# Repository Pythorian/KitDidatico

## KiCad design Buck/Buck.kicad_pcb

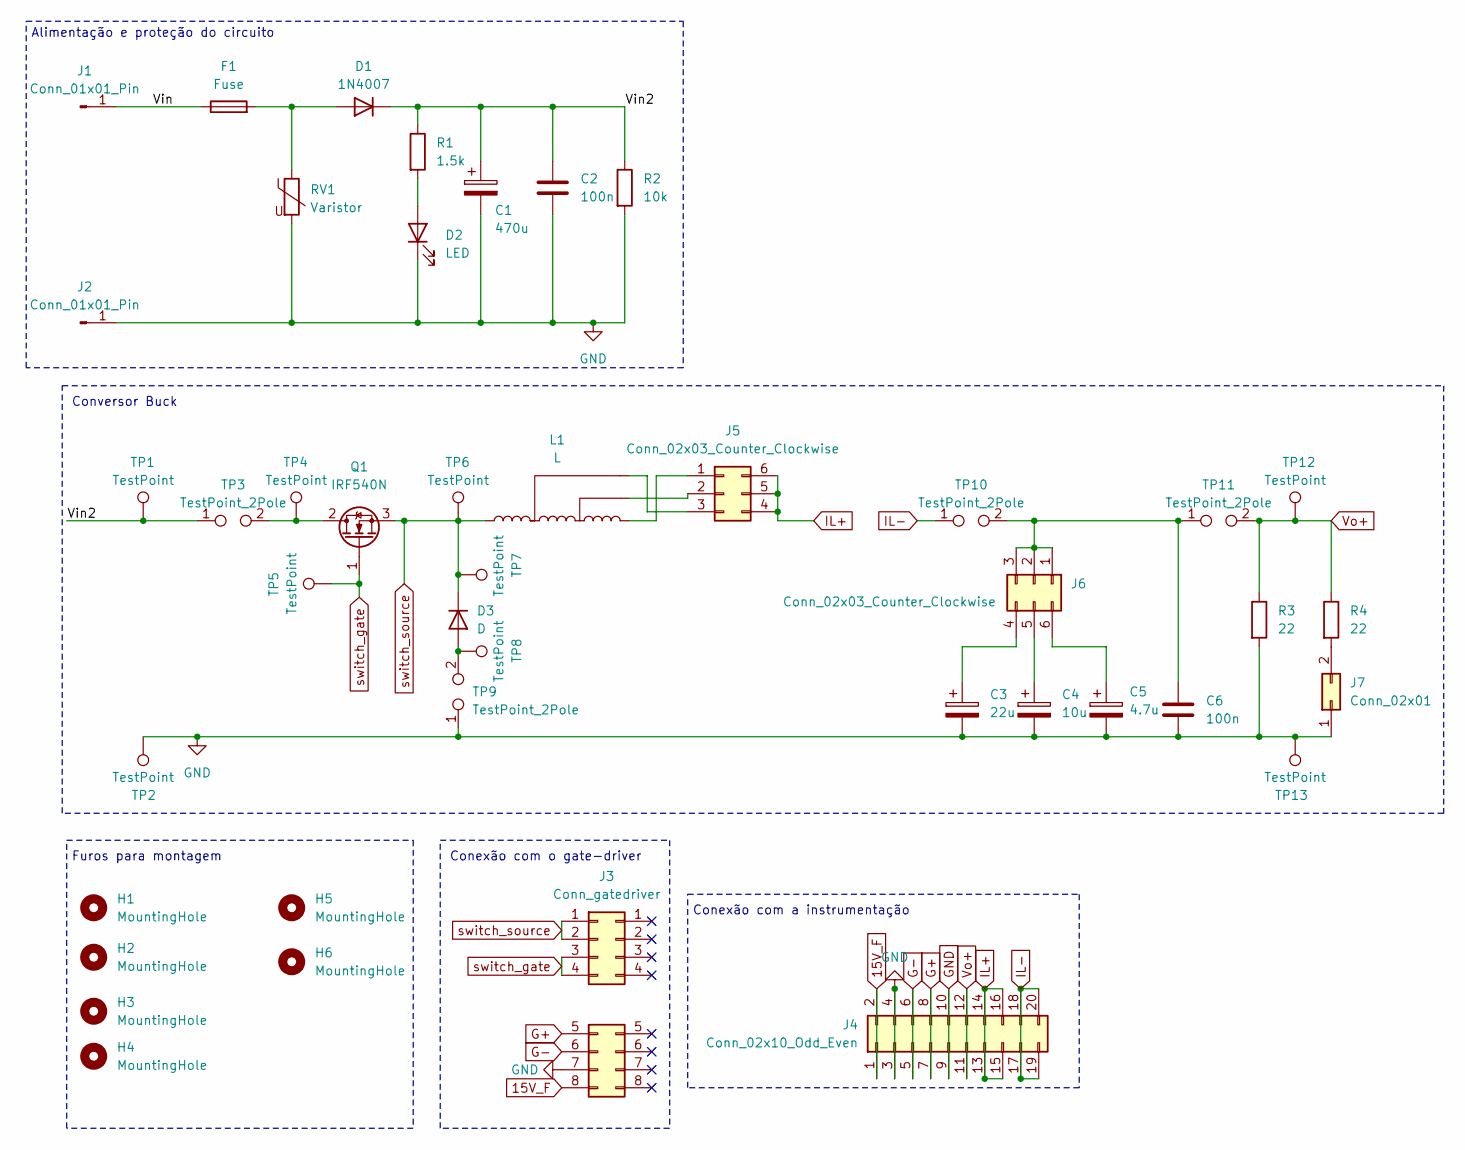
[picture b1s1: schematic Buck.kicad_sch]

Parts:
C1: 470u; CP_Radial_D16.0mm_P7.50mm
C2, C6: 100n; C_Disc_D5.0mm_W2.5mm_P5.00mm
C3: 22u; CP_Radial_D6.3mm_P2.50mm
C4: 10u; CP_Radial_D5.0mm_P2.00mm
C5: 4.7u; CP_Radial_D5.0mm_P2.00mm
D1: 1N4007; D_DO-41_SOD81_P10.16mm_Horizontal
D2: LED; LED_D3.0mm
D3: D; TO-220-2_Horizontal_TabDown
F1: Fuse
H1, H2, H3, H4, H5, H6: MountingHole; Furo
J1, J2: Conn_01x01_Pin; Banana_Jack_1Pin
J3: Conn_gatedriver; GateDriver
J4: Conn_02x10_Odd_Even; PinSocket_2x10_P2.54mm_Horizontal
J5, J6: Conn_02x03_Counter_Clockwise; PinHeader_2x03_P2.54mm_Vertical
J7: Conn_02x01; PinHeader_2x02_P2.54mm_Vertical
L1: L; Inductor_buck
Q1: IRF540N; TO-220-3_Horizontal_TabDown
R1: 1.5k; R_Axial_DIN0204_L3.6mm_D1.6mm_P7.62mm_Horizontal
R2: 10k; R_Axial_DIN0204_L3.6mm_D1.6mm_P7.62mm_Horizontal
R3, R4: 22; R_Axial_Power_L50.0mm_W9.0mm_P55.88mm
RV1: Varistor; RV_Disc_D7mm_W3.4mm_P5mm
TP1, TP2, TP4, TP5, TP6, TP7, TP8, TP12, TP13: TestPoint; TestPoint_Loop_D2.60mm_Drill1.6mm_Beaded
TP3, TP9, TP10, TP11: TestPoint_2Pole; Testpoint_current

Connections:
15V_F: J3.8 (Pin_15), J4.1, J4.2
/Vin: F1.1, J1.1
/Vin2: C1.1, C2.1, D1.1 (K), R1.1, R2.1, TP1.1, TP3.1
G+: J3.5 (Pin_9), J4.7, J4.8
G-: J3.6 (Pin_11), J4.5, J4.6
GND: C1.2, C2.2, C3.2, C4.2, C5.2, C6.2, D2.1 (K), J2.1, J3.7 (Pin_13), J4.3, J4.4, J4.9, J4.10, J7.1, R2.2, R3.2, RV1.2, TP2.1, TP9.1, TP13.1; also elsewhere on the board
IL+: J4.13, J4.14, J4.15, J4.16, J5.4, J5.5, J5.6
IL-: J4.17, J4.18, J4.19, J4.20, TP10.1
unnamed: D1.2 (A), F1.2, RV1.1
unnamed: D2.2 (A), R1.2
unnamed: D3.2 (A), TP8.1, TP9.2
unnamed: J5.1, L1.4
unnamed: J5.2, L1.3
unnamed: J5.3, L1.2
unnamed: C6.1, J6.1, J6.2, J6.3, TP10.2, TP11.1
unnamed: C3.1, J6.4
unnamed: C4.1, J6.5
unnamed: C5.1, J6.6
unnamed 18: J7.2, R4.2; also elsewhere on the board
unnamed: Q1.2 (D), TP3.2, TP4.1
Vo+: J4.11, J4.12, R3.1, R4.1, TP11.2, TP12.1; also elsewhere on the board
switch_gate: J3.3 (Pin_5), J3.4 (Pin_7), Q1.1 (G), TP5.1
switch_source: D3.1 (K), J3.1, J3.2 (Pin_3), L1.1, Q1.3 (S), TP6.1, TP7.1

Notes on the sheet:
Conversor Buck
Conexão com o gate-driver
Alimentação e proteção do circuito
Furos para montagem
Conexão com a instrumentação

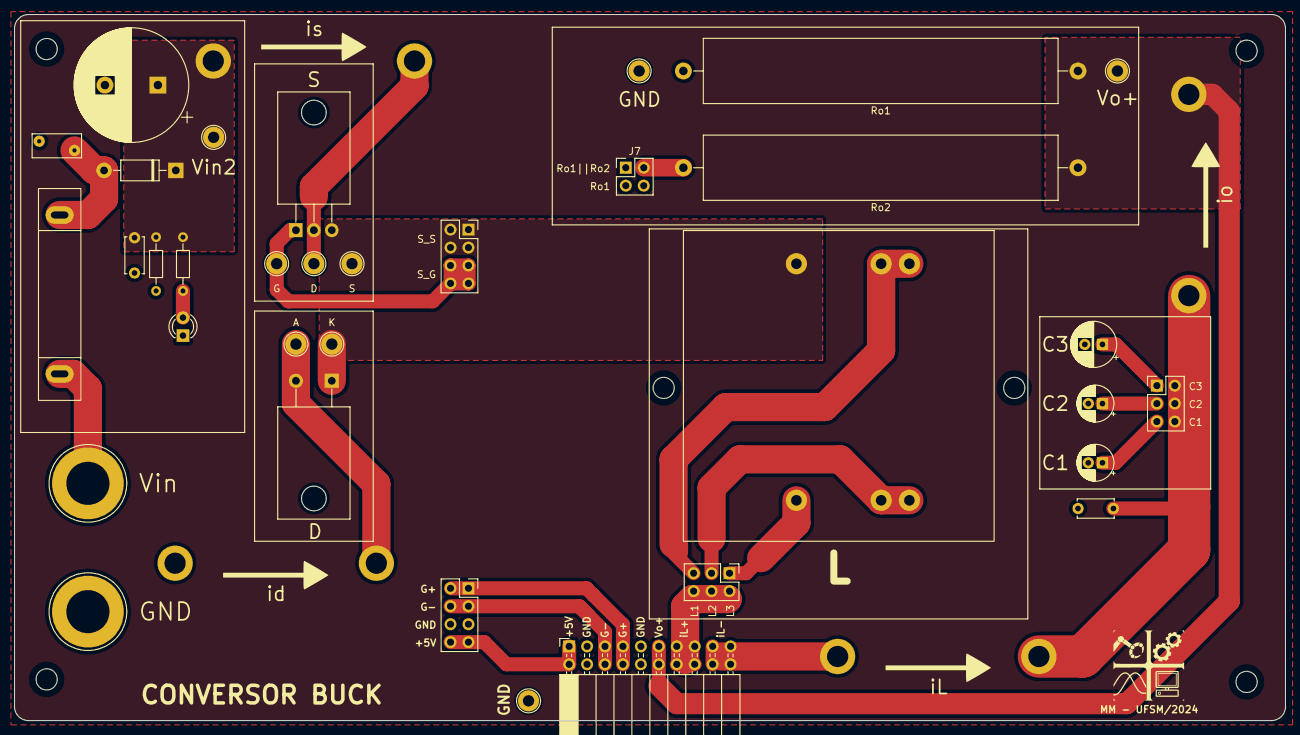
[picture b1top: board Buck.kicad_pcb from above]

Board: 2 copper layers, 180.0 x 100.0 mm, 43 parts (0 on the bottom side), 23 nets.

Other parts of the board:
Ro1, Ro2: 22; R_Axial_Power_L50.0mm_W9.0mm_P55.88mm

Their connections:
GND: Ro1.2; also elsewhere on the board
unnamed 18: Ro2.2; also elsewhere on the board
Vo+: Ro1.1, Ro2.1; also elsewhere on the board

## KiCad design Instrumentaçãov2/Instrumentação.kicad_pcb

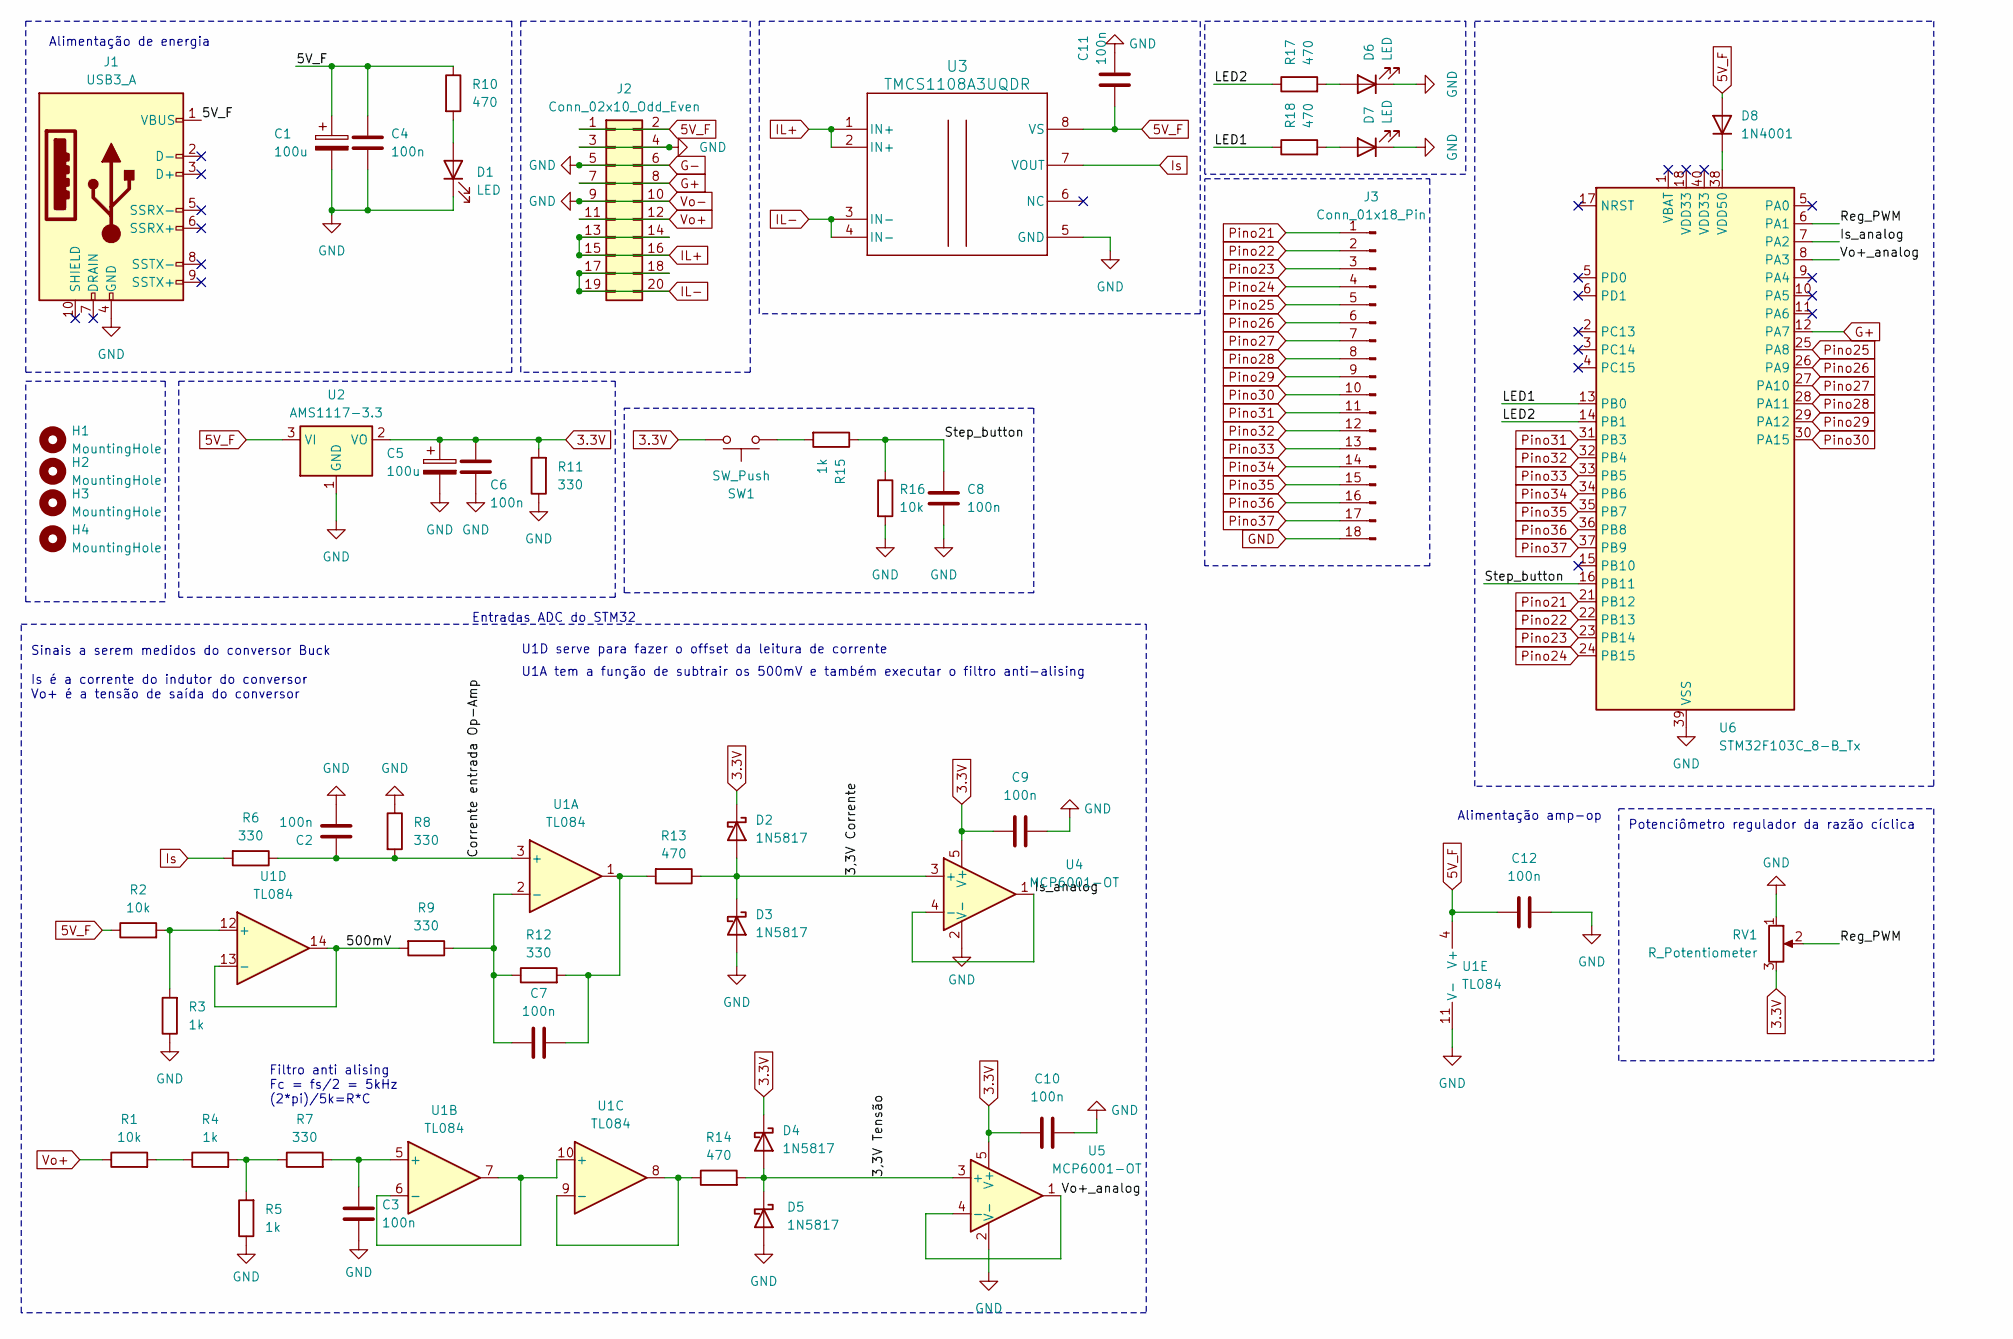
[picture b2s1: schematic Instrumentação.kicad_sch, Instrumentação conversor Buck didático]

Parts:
C1, C5: 100u; CP_Radial_D6.3mm_P2.50mm
C2, C3, C4, C6, C7, C8, C9, C10, C11, C12: 100n; C_Disc_D5.0mm_W2.5mm_P5.00mm
D1, D6, D7: LED; LED_D3.0mm
D2, D3, D4, D5: 1N5817; D_DO-41_SOD81_P10.16mm_Horizontal
D8: 1N4001; D_DO-41_SOD81_P10.16mm_Horizontal
H1, H2, H3, H4: MountingHole; Furo
J1: USB3_A; USB_A_Molex_67643_Horizontal
J2: Conn_02x10_Odd_Even; PinHeader_2x10_P2.54mm_Horizontal
J3: Conn_01x18_Pin; PinHeader_1x18_P2.54mm_Vertical
R1, R2, R16: 10k; R_Axial_DIN0204_L3.6mm_D1.6mm_P7.62mm_Horizontal
R3, R4, R5, R15: 1k; R_Axial_DIN0204_L3.6mm_D1.6mm_P7.62mm_Horizontal
R6, R7, R8, R9, R11, R12: 330; R_Axial_DIN0204_L3.6mm_D1.6mm_P7.62mm_Horizontal
R10, R13, R14, R17, R18: 470; R_Axial_DIN0204_L3.6mm_D1.6mm_P7.62mm_Horizontal
RV1: R_Potentiometer; Potentiometer_Alps_RK163_Single_Horizontal
SW1: SW_Push; SW_PUSH_6mm
U1: TL084; DIP-14_W7.62mm_Socket
U2: AMS1117-3.3; SOT-223-3_TabPin2
U3: TMCS1108A3UQDR; D0008A-IPC_A
U4, U5: MCP6001-OT; SOT-23-5
U6: STM32F103C_8-B_Tx; DIP-40_W15.24mm_Socket_LongPads

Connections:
3.3V: C5.1, C6.2, C9.1, C10.1, D2.1 (K), D4.1 (K), R11.2, RV1.3, SW1.2, U2.2 (VO), U4.5 (V+), U5.5 (V+)
5V_F: C1.1, C4.2, C11.2, C12.2, D8.2 (A), J1.1 (VBUS), J2.1, J2.2, R2.1, R10.1, U1.4 (V+), U2.3 (VI), U3.8 (VS)
/3,3V Corrente: D2.2 (A), D3.1 (K), R13.1, U4.3 (+)
/3,3V Tensão: D4.2 (A), D5.1 (K), R14.2, U5.3 (+)
/500mV: R9.2, U1.13 (-), U1.14
/Corrente entrada Op-Amp: C2.2, R6.1, R8.2, U1.3 (+)
/Is_analog: U4.1, U4.4 (-), U6.7 (PA2)
/LED1: R18.1, U6.13 (PB0)
/LED2: R17.1, U6.14 (PB1)
/Reg_PWM: RV1.2, U6.6 (PA1)
/Step_button: C8.2, R15.1, R16.1, U6.16 (PB11)
/Vo+_analog: U5.1, U5.4 (-), U6.8 (PA3)
G+: J2.7, J2.8, U6.12 (PA7)
G-: C1.2, C2.1, C3.1, C4.1, C5.2, C6.1, C8.1, C9.2, C10.2, C11.1, C12.1, D1.1 (K), D3.2 (A), D5.2 (A), D6.1 (K), D7.1 (K), J1.4 (GND), J2.3, J2.4, J2.5, J2.6, J2.9, J2.10, J3.18, R3.1, R5.1, R8.1, R11.1, R16.2, RV1.1, U1.11 (V-), U2.1 (GND), U3.5 (GND), U4.2 (V-), U5.2 (V-), U6.19 (VSS), U6.20 (VSS), U6.39 (VSS)
IL+: J2.13, J2.14, J2.15, J2.16, U3.1 (IN+), U3.2 (IN+)
IL-: J2.17, J2.18, J2.19, J2.20, U3.3 (IN-), U3.4 (IN-)
Is: R6.2, U3.7 (VOUT)
unnamed: C7.2, R12.2, R13.2, U1.1
unnamed: D1.2 (A), R10.2
unnamed: D6.2 (A), R17.2
unnamed: D7.2 (A), R18.2
unnamed: D8.1 (K), U6.38 (VDD50)
unnamed: R1.2, R4.1
unnamed: R4.2, R5.2, R7.1
unnamed: R15.2, SW1.1
unnamed: C7.1, R9.1, R12.1, U1.2 (-)
unnamed: C3.2, R7.2, U1.5 (+)
unnamed: U1.6 (-), U1.7, U1.10 (+)
unnamed: R14.1, U1.8, U1.9 (-)
unnamed: R2.2, R3.2, U1.12 (+)
Pino21: J3.1, U6.21 (PB12)
Pino22: J3.2, U6.22 (PB13)
Pino23: J3.3, U6.23 (PB14)
Pino24: J3.4, U6.24 (PB15)
Pino25: J3.5, U6.25 (PA8)
Pino26: J3.6, U6.26 (PA9)
Pino27: J3.7, U6.27 (PA10)
Pino28: J3.8, U6.28 (PA11)
Pino29: J3.9, U6.29 (PA12)
Pino30: J3.10, U6.30 (PA15)
Pino31: J3.11, U6.31 (PB3)
Pino32: J3.12, U6.32 (PB4)
Pino33: J3.13, U6.33 (PB5)
Pino34: J3.14, U6.34 (PB6)
Pino35: J3.15, U6.35 (PB7)
Pino36: J3.16, U6.36 (PB8)
Pino37: J3.17, U6.37 (PB9)
Vo+: J2.11, J2.12, R1.1

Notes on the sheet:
U1D serve para fazer o offset da leitura de corrente
Alimentação de energia
Potenciômetro regulador da razão cíclica
Sinais a serem medidos do conversor Buck Is é a corrente do indutor do conversor Vo+ é a tensão de saída do conversor
Entradas ADC do STM32
Alimentação amp-op
Filtro anti alising Fc = fs/2 = 5kHz (2*pi)/5k=R*C
U1A tem a função de subtrair os 500mV e também executar o filtro anti-alising

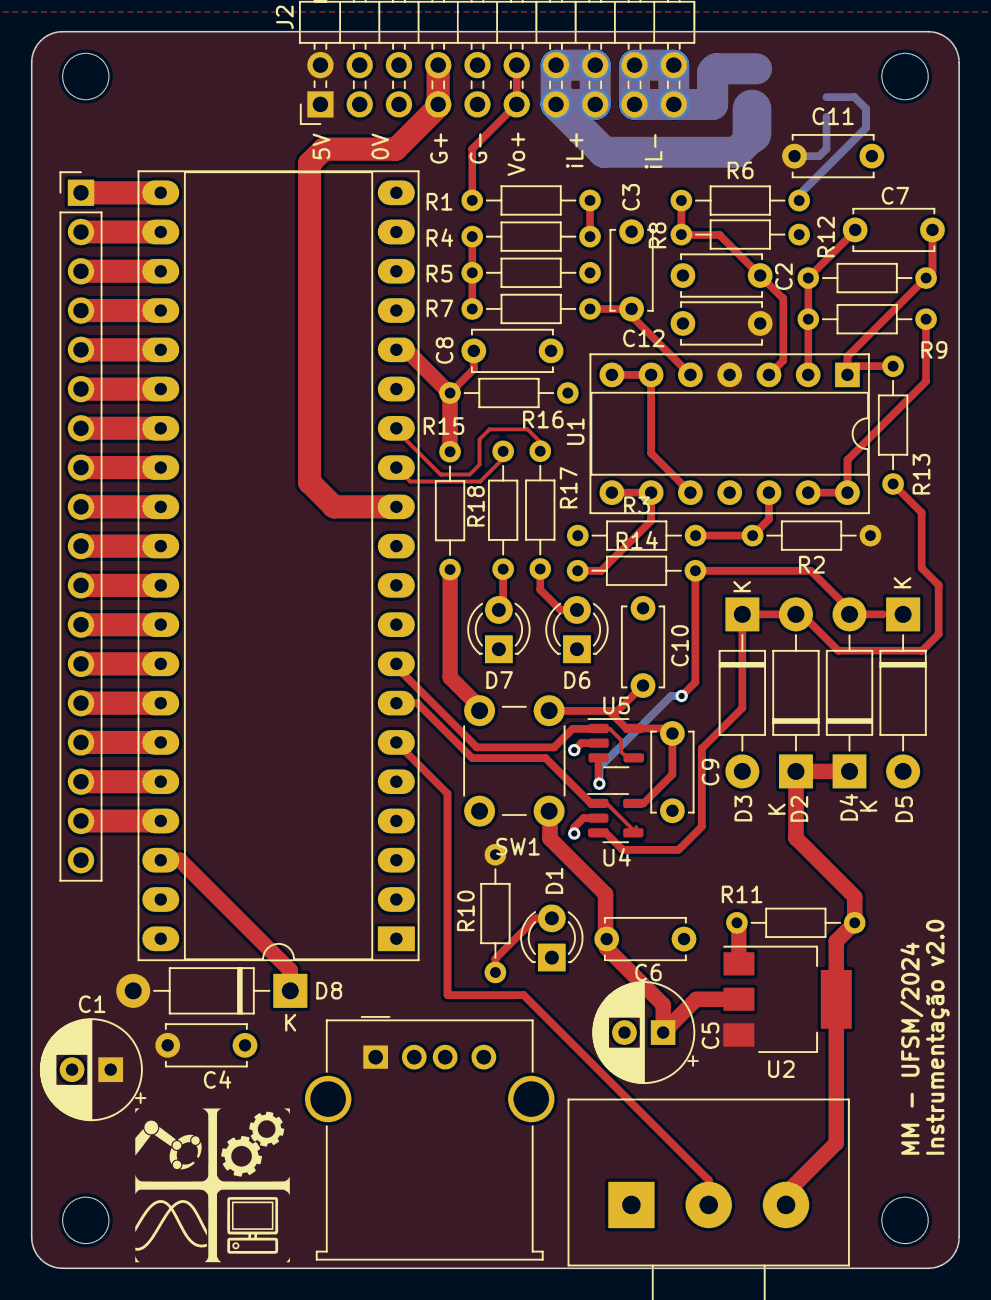
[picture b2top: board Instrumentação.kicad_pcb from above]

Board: 2 copper layers, 60.0 x 80.0 mm, 53 parts (1 on the bottom side), 48 nets.

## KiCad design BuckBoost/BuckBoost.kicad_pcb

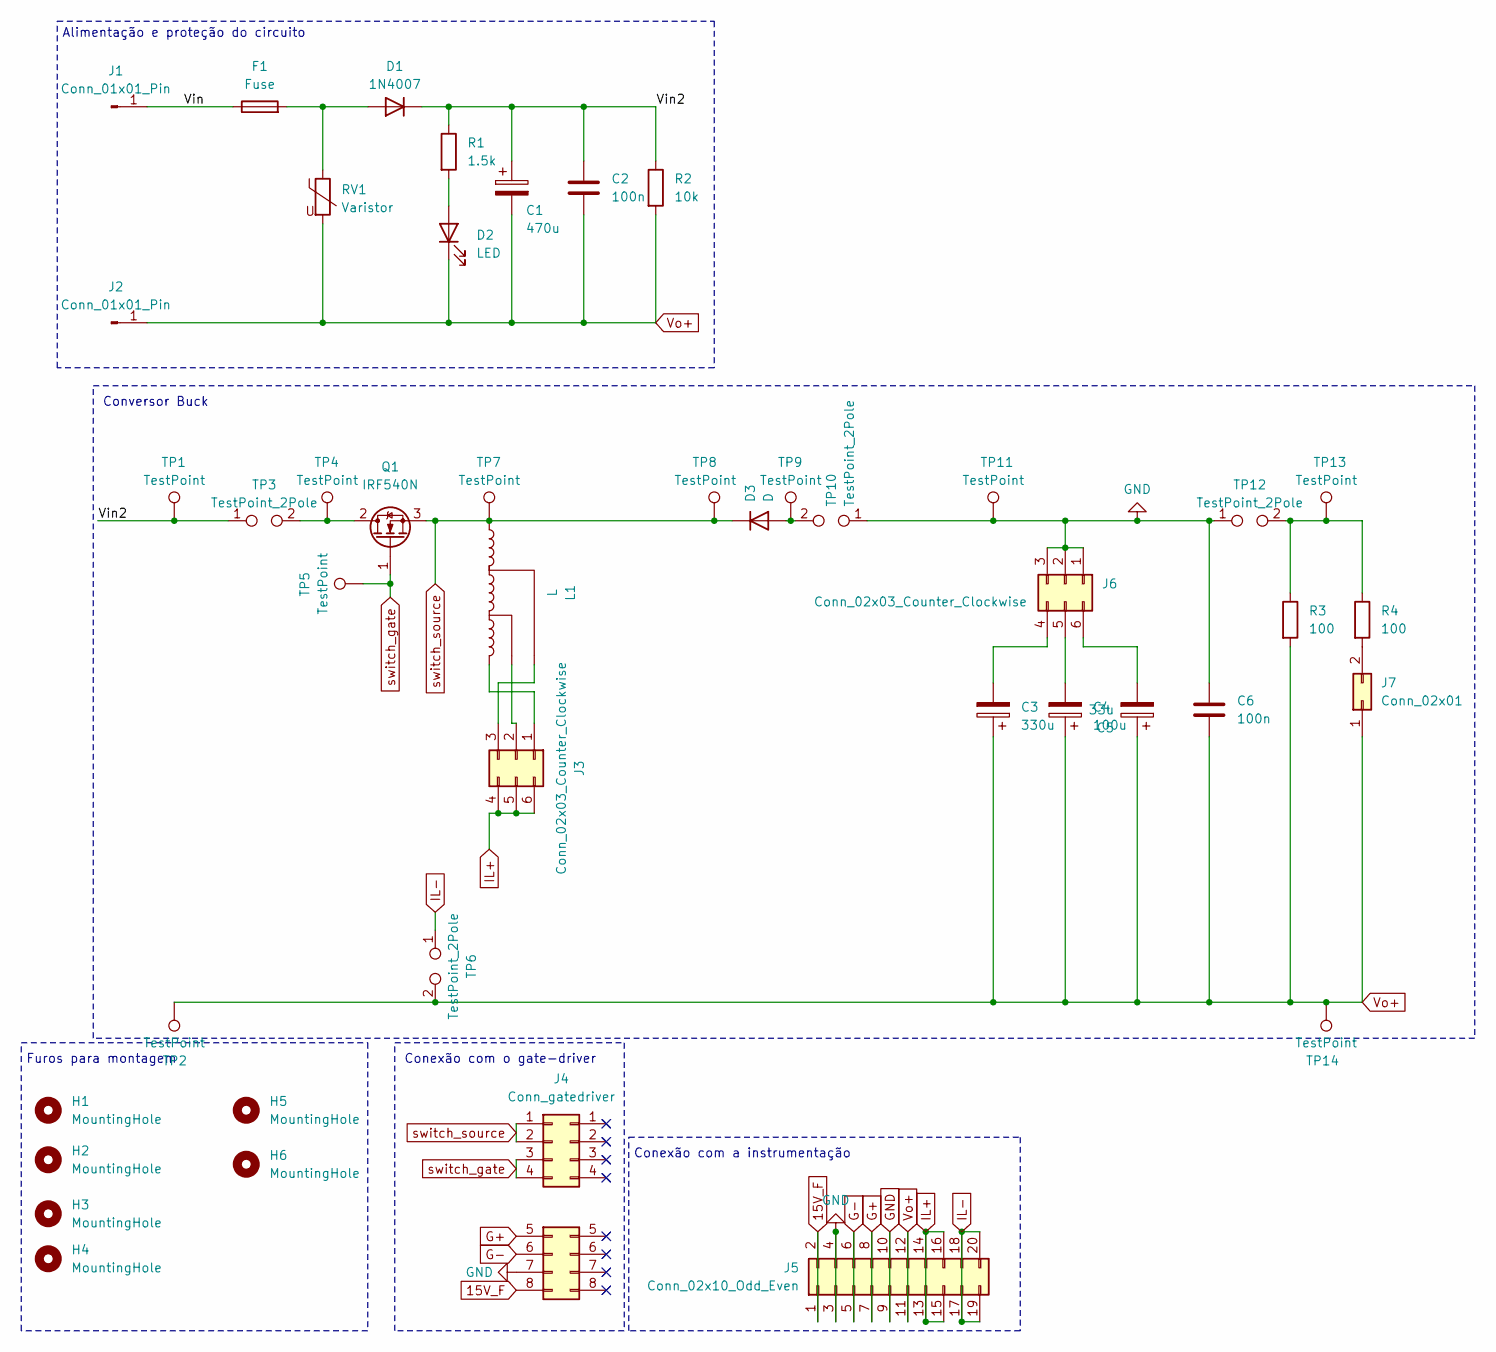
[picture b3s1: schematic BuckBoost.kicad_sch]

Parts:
C1: 470u; CP_Radial_D16.0mm_P7.50mm
C2, C6: 100n; C_Disc_D5.0mm_W2.5mm_P5.00mm
C3: 330u; CP_Radial_D10.0mm_P5.00mm
C4: 100u; CP_Radial_D10.0mm_P5.00mm
C5: 33u; CP_Radial_D6.3mm_P2.50mm
D1: 1N4007; D_DO-41_SOD81_P10.16mm_Horizontal
D2: LED; LED_D3.0mm
D3: D; TO-220-2_Horizontal_TabDown
F1: Fuse
H1, H2, H3, H4, H5, H6: MountingHole; Furo
J1, J2: Conn_01x01_Pin; Banana_Jack_1Pin
J3, J6: Conn_02x03_Counter_Clockwise; PinHeader_2x03_P2.54mm_Vertical
J4: Conn_gatedriver; GateDriver
J5: Conn_02x10_Odd_Even; PinSocket_2x10_P2.54mm_Horizontal
J7: Conn_02x01; PinHeader_2x02_P2.54mm_Vertical
L1: L; Inductor_buckboost
Q1: IRF540N; TO-220-3_Horizontal_TabDown
R1: 1.5k; R_Axial_DIN0204_L3.6mm_D1.6mm_P7.62mm_Horizontal
R2: 10k; R_Axial_DIN0204_L3.6mm_D1.6mm_P7.62mm_Horizontal
R3, R4: 100; R_Axial_Power_L50.0mm_W9.0mm_P55.88mm
RV1: Varistor; RV_Disc_D7mm_W3.4mm_P5mm
TP1, TP2, TP4, TP5, TP7, TP8, TP9, TP11, TP13, TP14: TestPoint; TestPoint_Loop_D2.60mm_Drill1.6mm_Beaded
TP3, TP6, TP10, TP12: TestPoint_2Pole; Testpoint_current

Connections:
15V_F: J4.8 (Pin_15), J5.1, J5.2
/Vin: F1.1, J1.1
/Vin2: C1.1, C2.1, D1.1 (K), R1.1, R2.1, TP1.1, TP3.1; also elsewhere on the board
G+: J4.5 (Pin_9), J5.7, J5.8
G-: J4.6 (Pin_11), J5.5, J5.6
GND: C6.1, J4.7 (Pin_13), J5.3, J5.4, J5.9, J5.10, J6.1, J6.2, J6.3, TP10.1, TP11.1, TP12.1
IL+: J3.4, J3.5, J3.6, J5.13, J5.14, J5.15, J5.16
IL-: J5.17, J5.18, J5.19, J5.20, TP6.1
unnamed: D1.2 (A), F1.2, RV1.1
unnamed: D2.2 (A), R1.2
unnamed: D3.2 (A), TP9.1, TP10.2
unnamed 11: J3.1, L1.4; also elsewhere on the board
unnamed 12: J3.2, L1.3; also elsewhere on the board
unnamed 13: J3.3, L1.2; also elsewhere on the board
unnamed: C3.2, J6.4
unnamed: C4.2, J6.5
unnamed: C5.2, J6.6
unnamed 17: J7.2, R4.2; also elsewhere on the board
unnamed: Q1.2 (D), TP3.2, TP4.1
unnamed 19: R3.1, R4.1, TP12.2, TP13.1; also elsewhere on the board
Vo+: C1.2, C2.2, C3.1, C4.1, C5.1, C6.2, D2.1 (K), J2.1, J5.11, J5.12, J7.1, R2.2, R3.2, RV1.2, TP2.1, TP6.2, TP14.1; also elsewhere on the board
switch_gate: J4.3 (Pin_5), J4.4 (Pin_7), Q1.1 (G), TP5.1
switch_source: D3.1 (K), J4.1, J4.2 (Pin_3), L1.1, Q1.3 (S), TP7.1, TP8.1; also elsewhere on the board

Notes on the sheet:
Conversor Buck
Conexão com o gate-driver
Alimentação e proteção do circuito
Furos para montagem
Conexão com a instrumentação

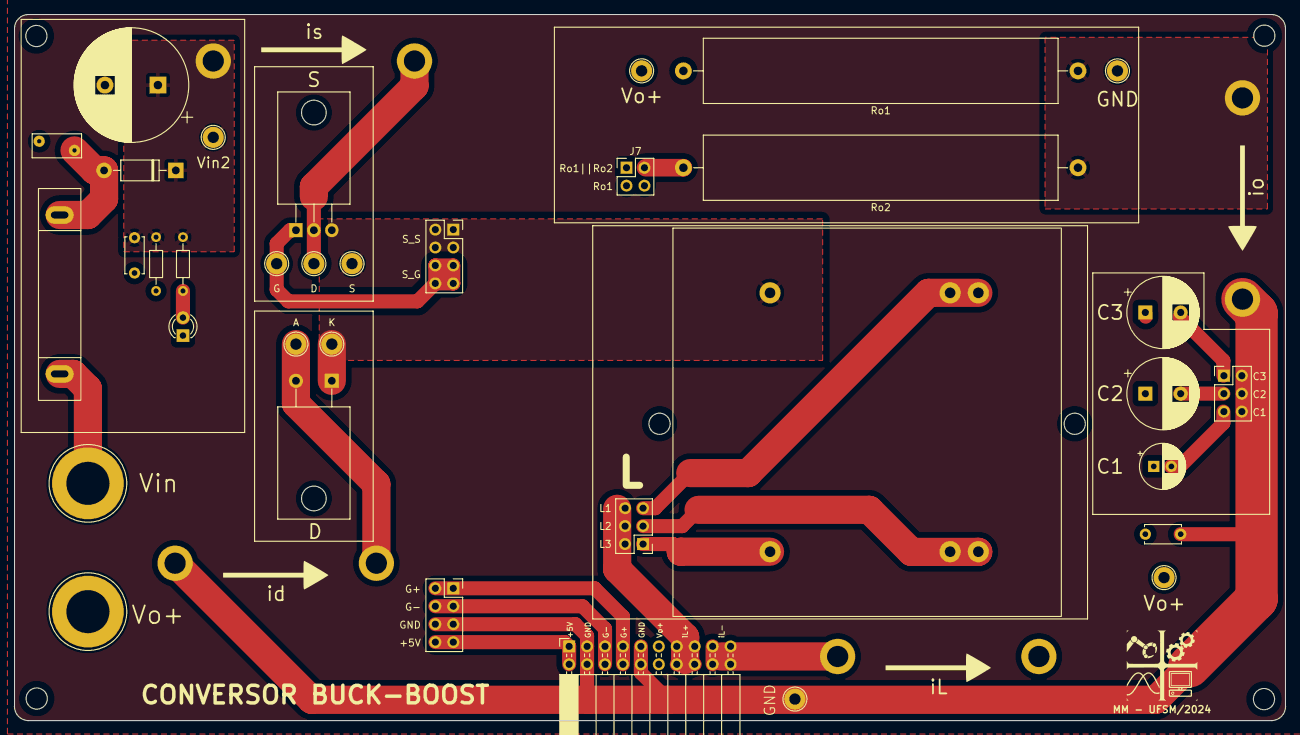
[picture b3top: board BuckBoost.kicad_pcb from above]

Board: 2 copper layers, 180.0 x 100.0 mm, 44 parts (0 on the bottom side), 23 nets.

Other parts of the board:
L: L; Inductor_buckboost
Ro1, Ro2: 100; R_Axial_Power_L50.0mm_W9.0mm_P55.88mm
Vin2: TestPoint; TestPoint_Loop_D2.60mm_Drill1.6mm_Beaded

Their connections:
/Vin2: Vin2.1; also elsewhere on the board
unnamed 11: L.4; also elsewhere on the board
unnamed 12: L.3; also elsewhere on the board
unnamed 13: L.2; also elsewhere on the board
unnamed 17: Ro2.2; also elsewhere on the board
unnamed 19: Ro1.1, Ro2.1; also elsewhere on the board
Vo+: Ro1.2; also elsewhere on the board
switch_source: L.1; also elsewhere on the board

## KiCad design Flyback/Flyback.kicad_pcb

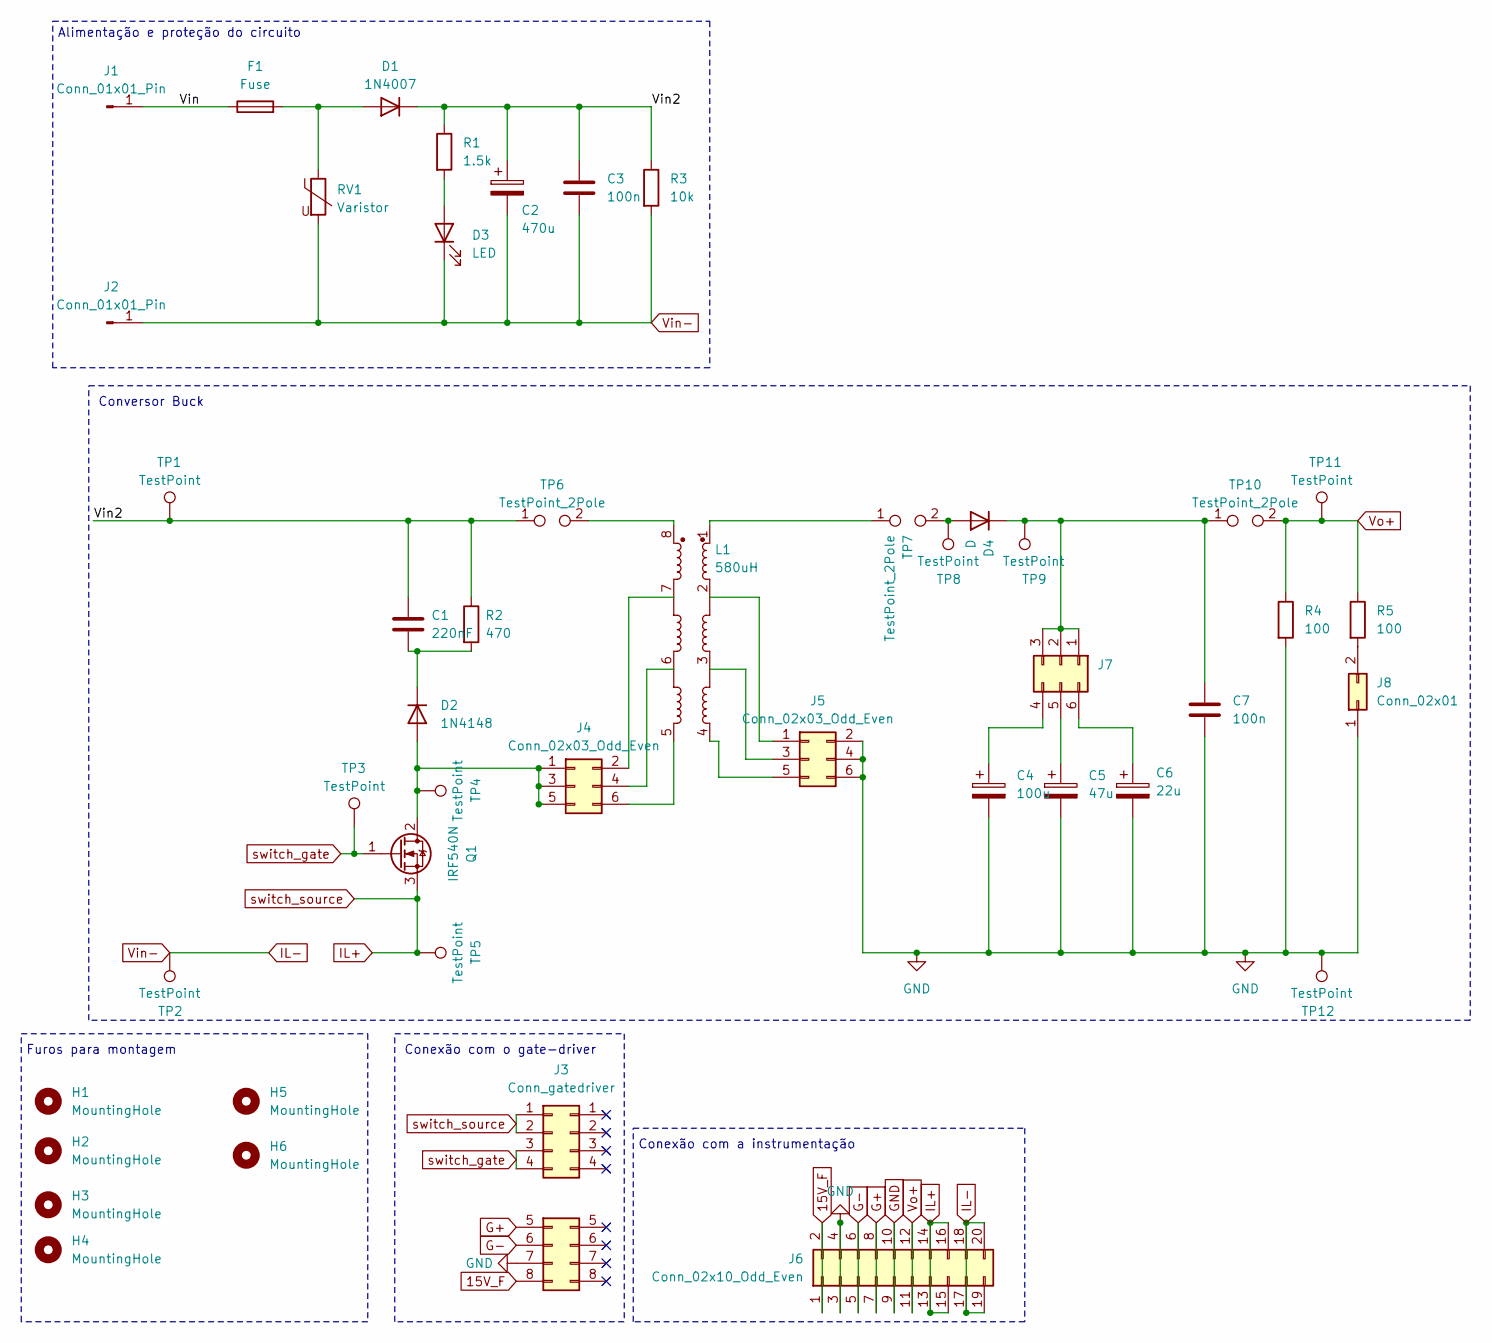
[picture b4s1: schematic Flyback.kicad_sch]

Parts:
C1: 220nF; C_Disc_D5.0mm_W2.5mm_P5.00mm
C2: 470u; CP_Radial_D16.0mm_P7.50mm
C3, C7: 100n; C_Disc_D5.0mm_W2.5mm_P5.00mm
C4: 100u; CP_Radial_D10.0mm_P5.00mm
C5: 47u; CP_Radial_D6.3mm_P2.50mm
C6: 22u; CP_Radial_D6.3mm_P2.50mm
D1: 1N4007; D_DO-41_SOD81_P10.16mm_Horizontal
D2: 1N4148; D_DO-35_SOD27_P7.62mm_Horizontal
D3: LED; LED_D3.0mm
D4: D; TO-220-2_Horizontal_TabDown
F1: Fuse
H1, H2, H3, H4, H5, H6: MountingHole; Furo
J1, J2: Conn_01x01_Pin; Banana_Jack_1Pin
J3: Conn_gatedriver; GateDriver
J4, J5: Conn_02x03_Odd_Even; PinHeader_2x03_P2.54mm_Vertical
J6: Conn_02x10_Odd_Even; PinSocket_2x10_P2.54mm_Horizontal
J7: Conn_02x03_Counter_Clockwise; PinHeader_2x03_P2.54mm_Vertical
J8: Conn_02x01; PinHeader_2x02_P2.54mm_Vertical
L1: 580uH; Transformer_Flyback
Q1: IRF540N; TO-220-3_Horizontal_TabDown
R1: 1.5k; R_Axial_DIN0204_L3.6mm_D1.6mm_P7.62mm_Horizontal
R2: 470; R_Axial_Power_L20.0mm_W6.4mm_P25.40mm
R3: 10k; R_Axial_DIN0204_L3.6mm_D1.6mm_P7.62mm_Horizontal
R4, R5: 100; R_Axial_Power_L50.0mm_W9.0mm_P55.88mm
RV1: Varistor; RV_Disc_D7mm_W3.4mm_P5mm
TP1, TP2, TP3, TP4, TP5, TP8, TP9, TP11, TP12: TestPoint; TestPoint_Loop_D2.60mm_Drill1.6mm_Beaded
TP6, TP7, TP10: TestPoint_2Pole; Testpoint_current

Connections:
15V_F: J3.8 (Pin_15), J6.1, J6.2
/Vin: F1.1, J1.1
/Vin2: C1.1, C2.1, C3.1, D1.1 (K), R1.1, R2.1, R3.1, TP1.1, TP6.1
G+: J3.5 (Pin_9), J6.7, J6.8
G-: J3.6 (Pin_11), J6.5, J6.6
GND: C4.2, C5.2, C6.2, C7.2, J3.7 (Pin_13), J5.2, J5.4, J5.6, J6.3, J6.4, J6.9, J6.10, J8.1, R4.2, TP12.1; also elsewhere on the board
IL+: J3.1, J3.2 (Pin_3), J6.13, J6.14, J6.15, J6.16, Q1.3 (S), TP5.1
IL-: C2.2, C3.2, D3.1 (K), J2.1, J6.17, J6.18, J6.19, J6.20, R3.2, RV1.2, TP2.1
unnamed: D1.2 (A), F1.2, RV1.1
unnamed: D2.2 (A), J4.1, J4.3, J4.5, Q1.2 (D), TP4.1
unnamed: C1.2, D2.1 (K), R2.2
unnamed: D3.2 (A), R1.2
unnamed: D4.2 (A), TP7.2, TP8.1
unnamed: C7.1, D4.1 (K), J7.1, J7.2, J7.3, TP9.1, TP10.1
unnamed: J4.2, L1.7
unnamed: J4.4, L1.6
unnamed: J4.6, L1.5
unnamed: J5.1, L1.2
unnamed: J5.3, L1.3
unnamed: J5.5, L1.4
unnamed: C4.1, J7.4
unnamed: C5.1, J7.5
unnamed: C6.1, J7.6
unnamed 23: J8.2, R5.2; also elsewhere on the board
unnamed: L1.1, TP7.1
unnamed: L1.8, TP6.2
Vo+: J6.11, J6.12, R4.1, R5.1, TP10.2, TP11.1; also elsewhere on the board
switch_gate: J3.3 (Pin_5), J3.4 (Pin_7), Q1.1 (G), TP3.1

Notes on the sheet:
Conversor Buck
Conexão com o gate-driver
Alimentação e proteção do circuito
Furos para montagem
Conexão com a instrumentação

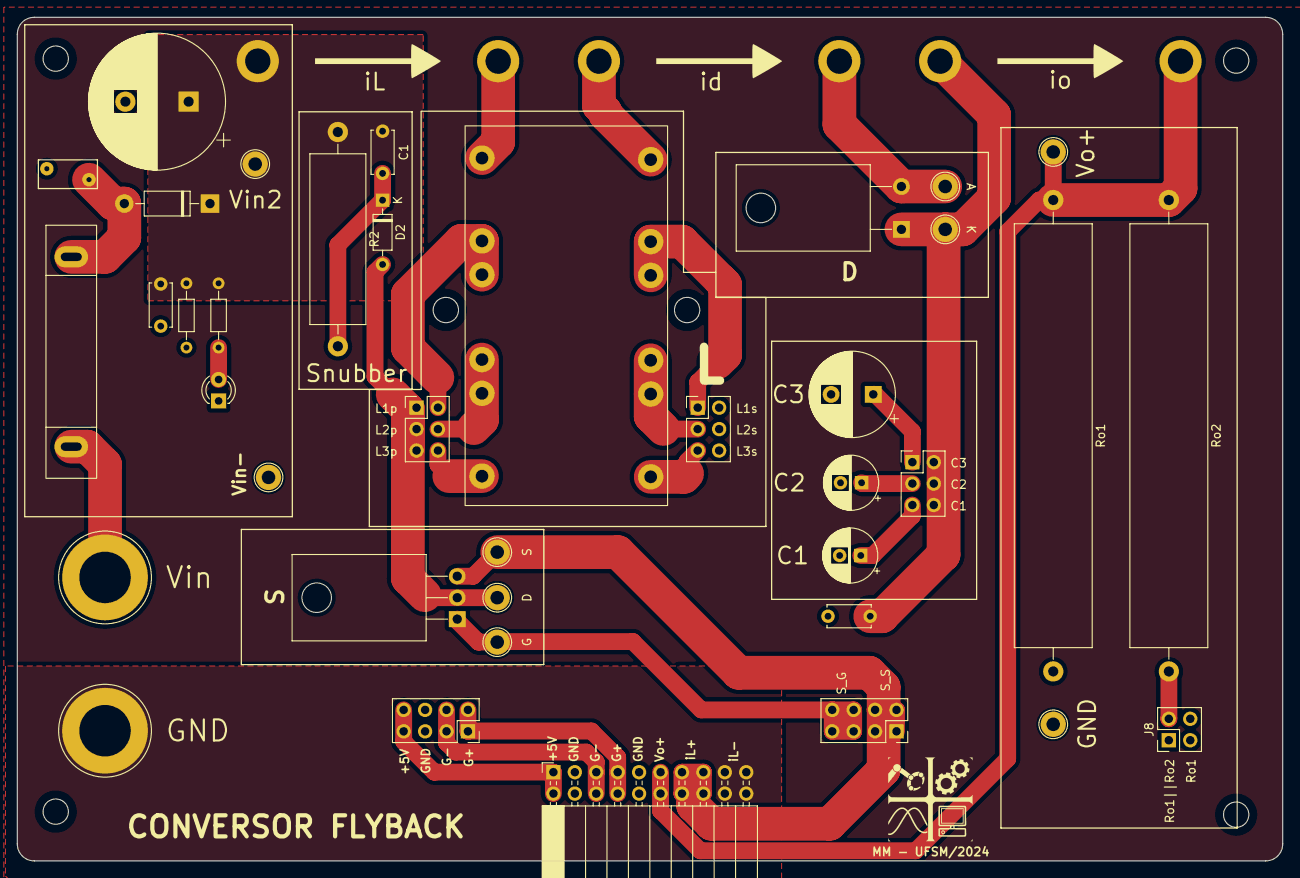
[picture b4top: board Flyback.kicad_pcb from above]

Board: 2 copper layers, 150.0 x 100.0 mm, 46 parts (0 on the bottom side), 28 nets.

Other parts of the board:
Ro1, Ro2: 100; R_Axial_Power_L50.0mm_W9.0mm_P55.88mm

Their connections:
GND: Ro1.2; also elsewhere on the board
unnamed 23: Ro2.2; also elsewhere on the board
Vo+: Ro1.1, Ro2.1; also elsewhere on the board

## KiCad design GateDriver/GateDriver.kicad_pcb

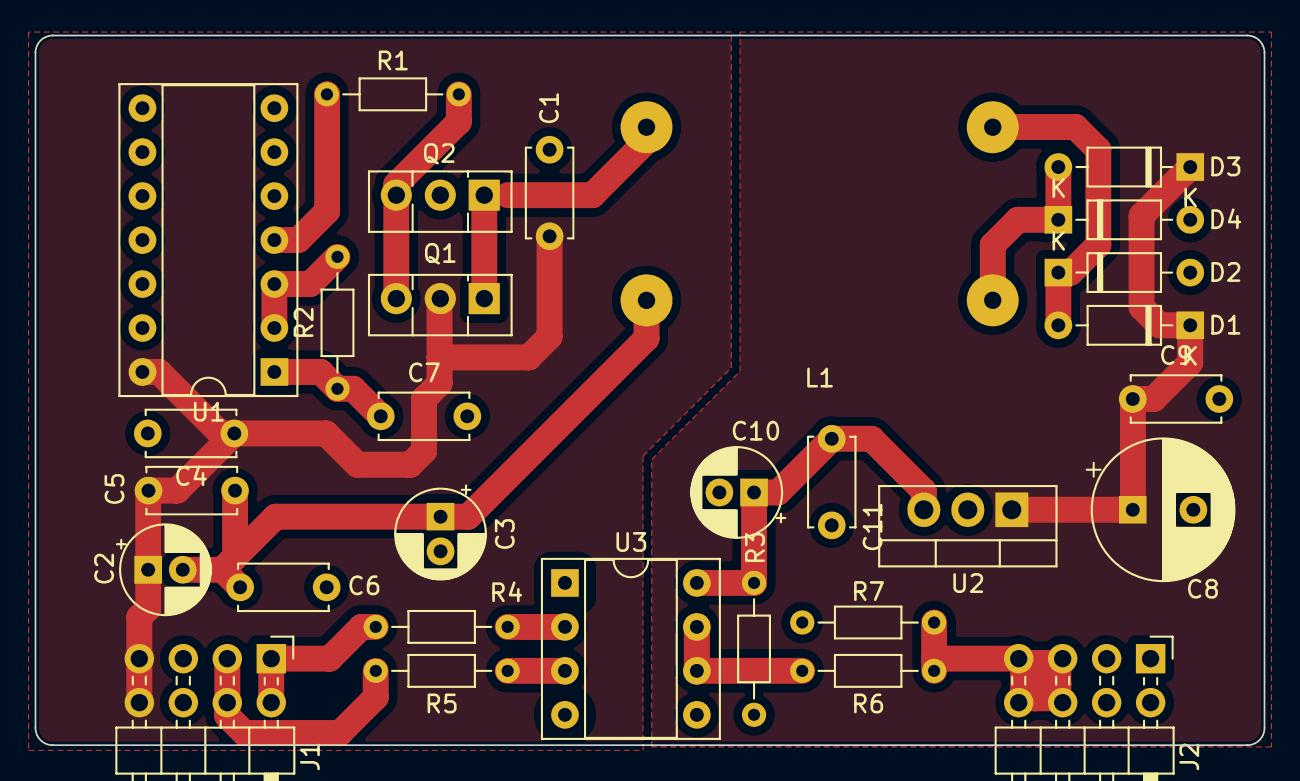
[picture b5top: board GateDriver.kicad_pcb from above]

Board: 2 copper layers, 71.0 x 41.0 mm, 30 parts (0 on the bottom side), 19 nets.

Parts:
C1, C4, C5, C6, C9, C11: 100n; C_Disc_D5.0mm_W2.5mm_P5.00mm
C2, C3, C10: 10u; CP_Radial_D5.0mm_P2.00mm
C7: 100p; C_Disc_D5.0mm_W2.5mm_P5.00mm
C8: 100u; CP_Radial_D8.0mm_P3.50mm
D1, D2, D3, D4: 1N4148; D_DO-35_SOD27_P7.62mm_Horizontal
J1, J2: Conn_02x04_Odd_Even; PinHeader_2x04_P2.54mm_Horizontal
L1: L_Coupled; Inductor_Coupled
Q1: BD135; TO-126-3_Vertical
Q2: BD136; TO-126-3_Vertical
R1, R3: 1k; R_Axial_DIN0204_L3.6mm_D1.6mm_P7.62mm_Horizontal
R2: 51k; R_Axial_DIN0204_L3.6mm_D1.6mm_P7.62mm_Horizontal
R4, R5: 100; R_Axial_DIN0204_L3.6mm_D1.6mm_P7.62mm_Horizontal
R6: 10; R_Axial_DIN0204_L3.6mm_D1.6mm_P7.62mm_Horizontal
R7: 10k; R_Axial_DIN0204_L3.6mm_D1.6mm_P7.62mm_Horizontal
U1: 74HC14; DIP-14_W7.62mm_Socket
U2: LM7815_TO220; TO-220-3_Vertical
U3: HCPL-3120; DIP-8_W7.62mm_Socket

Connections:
15V_F: C1.1, C2.1, C4.1, C5.1, J1.7, J1.8, Q1.2 (C), U1.14 (VCC)
/15V: C10.1, C11.1, R3.2, U2.3 (VO), U3.8 (VCC)
/Ret+: C8.1, C9.1, D1.1 (K), D3.1 (K), U2.1 (VI)
/Ret-: C8.2, C9.2, C10.2, C11.2, D2.2 (A), D4.2 (A), J2.1, J2.2, J2.3, J2.4, R3.1, R7.2, U2.2 (GND), U3.5 (VEE)
G+: J1.1, J1.2, R4.2
G-: J1.3, J1.4, R5.2
GND: C1.2, C3.2, C4.2, C6.2, C7.2, J1.5, J1.6, Q2.2 (C), U1.7 (GND)
unnamed: C2.2, C3.1, C5.2, C6.1, L1.2
unnamed: C7.1, R2.1, U1.1
unnamed: D1.2 (A), D2.1 (K), L1.3
unnamed: D3.2 (A), D4.1 (K), L1.4
unnamed: Q1.3 (B), Q2.3 (B), R1.2
unnamed: L1.1, Q1.1 (E), Q2.1 (E)
unnamed: R2.2, U1.2, U1.3
unnamed: R6.2, U3.6 (VO), U3.7 (VO)
unnamed: R4.1, U3.2 (A)
unnamed: R5.1, U3.3 (C)
Oscilador: R1.1, U1.4
Switch_Gate: J2.5, J2.6, J2.7, J2.8, R6.1, R7.1

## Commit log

2024-04-21 Add kit
